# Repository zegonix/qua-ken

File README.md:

**This repository has been moved to [another git server](https://git.krampf.ch/zegonix/qua-ken).**

# qua-ken
this repository holds the design resources for the open source keyboard 'qua-ken'. The qua-ken is heavily inspired by [Josef Adamčík](https://github.com/josefadamcik)'s [Sofle](https://github.com/josefadamcik/SofleKeyboard) and copies its layout. The qua-ken is basically a Sofle modified to meet my custom keyboard standards. The PCB is split into main board and daughter board which holds the connectors. The qua-ken uses more a powerful ARM controller with much more program memory allowing the use of more software features. For the connection of the two halves a 4P4C connector is used as the TRRS connector shorts some of the lines when plugging/unplugging the cable. Currently planned are PCB silicone dumbbell gasket mount and plate top mount. The case is planned as screwless design opening from the top for ease of access. I also think about using the ball catch system gaining popularity, but since I have no experience with mechanical design, I am unsure whether I can manage that in a reasonable amount of revisions.

# Status
~~I just started and am currently working on the PCB. Once the PCB is tested, I will start with the case.~~
I just got the PCBs, it works perfectly fine appart from the encoders, which only work if the left half is master (connected to the computer). I am now starting with the case design and will fix the encoders at some point (just software).

# Licensing
Software (QMK) is licensed under GPL 2.0, With PCB and case designs you are free to do as you will.

# Can you buy this keyboard when it's finished?
Yes and No. I will not open shop and sell the keyboard, but the resources are free and open, so you can order all the parts yourself.

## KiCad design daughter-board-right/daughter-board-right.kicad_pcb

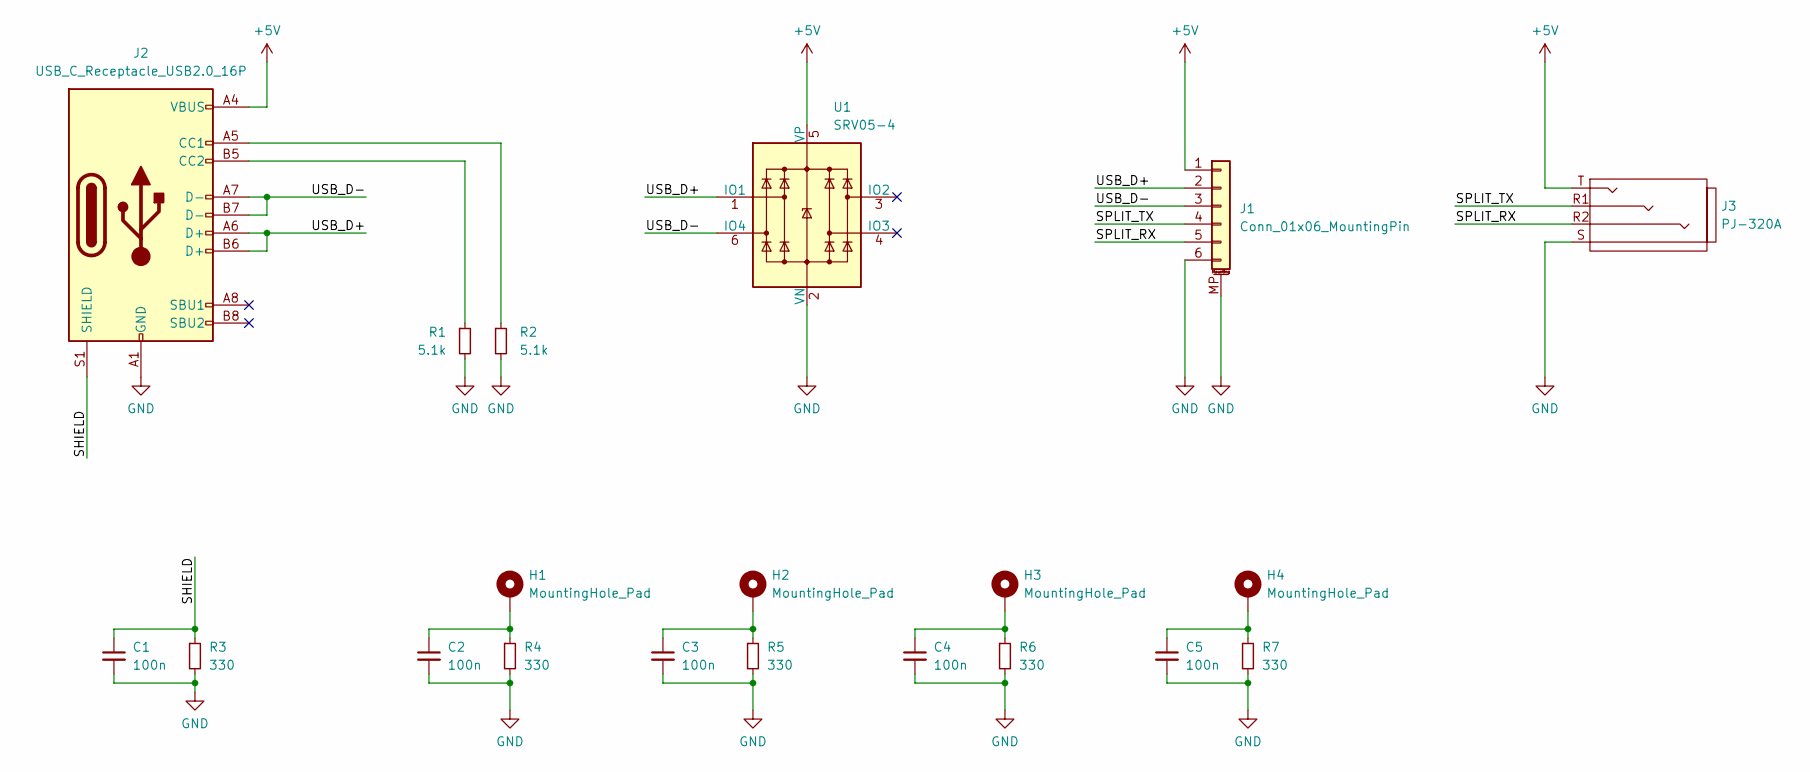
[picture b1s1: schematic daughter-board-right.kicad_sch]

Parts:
C1, C2, C3, C4, C5: 100n; C_0603_1608Metric
H1, H2, H3, H4: MountingHole_Pad; MountingHole_2.2mm_M2_DIN965_Pad_TopBottom
J1: Conn_01x06_MountingPin; JST_SH_SM06B-SRSS-TB_1x06-1MP_P1.00mm_Horizontal
J2: USB_C_Receptacle_USB2.0_16P; USB_C_Receptacle_HRO_TYPE-C-31-M-12
J3: PJ-320A; TRRS_Receptable
R1, R2: 5.1k; R_0603_1608Metric
R3, R4, R5, R6, R7: 330; R_0603_1608Metric
U1: SRV05-4; SOT-23-6-routable

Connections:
+5V: J1.1, J2.A4 (VBUS), J2.A9 (VBUS), J2.B4 (VBUS), J2.B9 (VBUS), J3.T, U1.5 (VP)
/SHIELD: C1.1, J2.S1 (SHIELD), R3.1
/SPLIT_RX: J1.5, J3.R2
/SPLIT_TX: J1.4, J3.R1
/USB_D+: J1.2, J2.A6 (D+), J2.B6 (D+), U1.1 (IO1)
/USB_D-: J1.3, J2.A7 (D-), J2.B7 (D-), U1.6 (IO4)
GND: C1.2, C2.2, C3.2, C4.2, C5.2, J1.6, J1.MP (MountPin), J2.A1 (GND), J2.A12 (GND), J2.B1 (GND), J2.B12 (GND), J3.S, R1.2, R2.2, R3.2, R4.2, R5.2, R6.2, R7.2, U1.2 (VN)
unnamed: C2.1, H1.1, R4.1
unnamed: C3.1, H2.1, R5.1
unnamed: C4.1, H3.1, R6.1
unnamed: C5.1, H4.1, R7.1
unnamed: J2.A5 (CC1), R2.1
unnamed: J2.B5 (CC2), R1.1

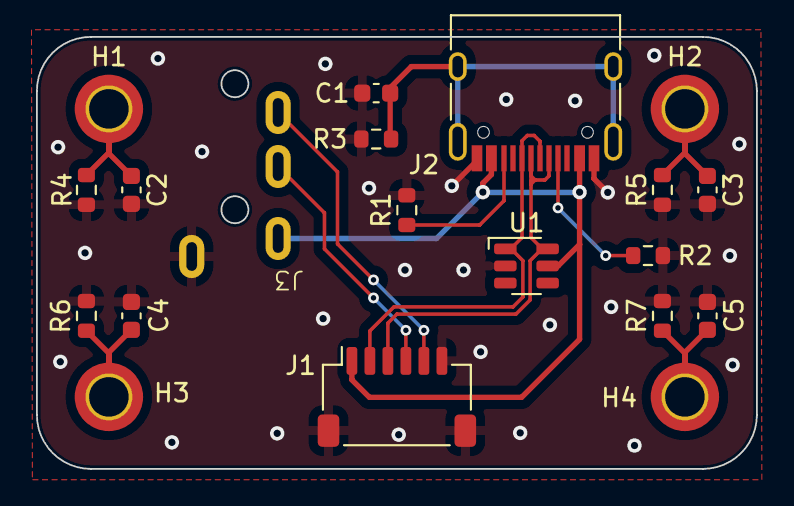
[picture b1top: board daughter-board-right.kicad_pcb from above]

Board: 2 copper layers, 40.0 x 24.0 mm, 20 parts (0 on the bottom side), 13 nets.

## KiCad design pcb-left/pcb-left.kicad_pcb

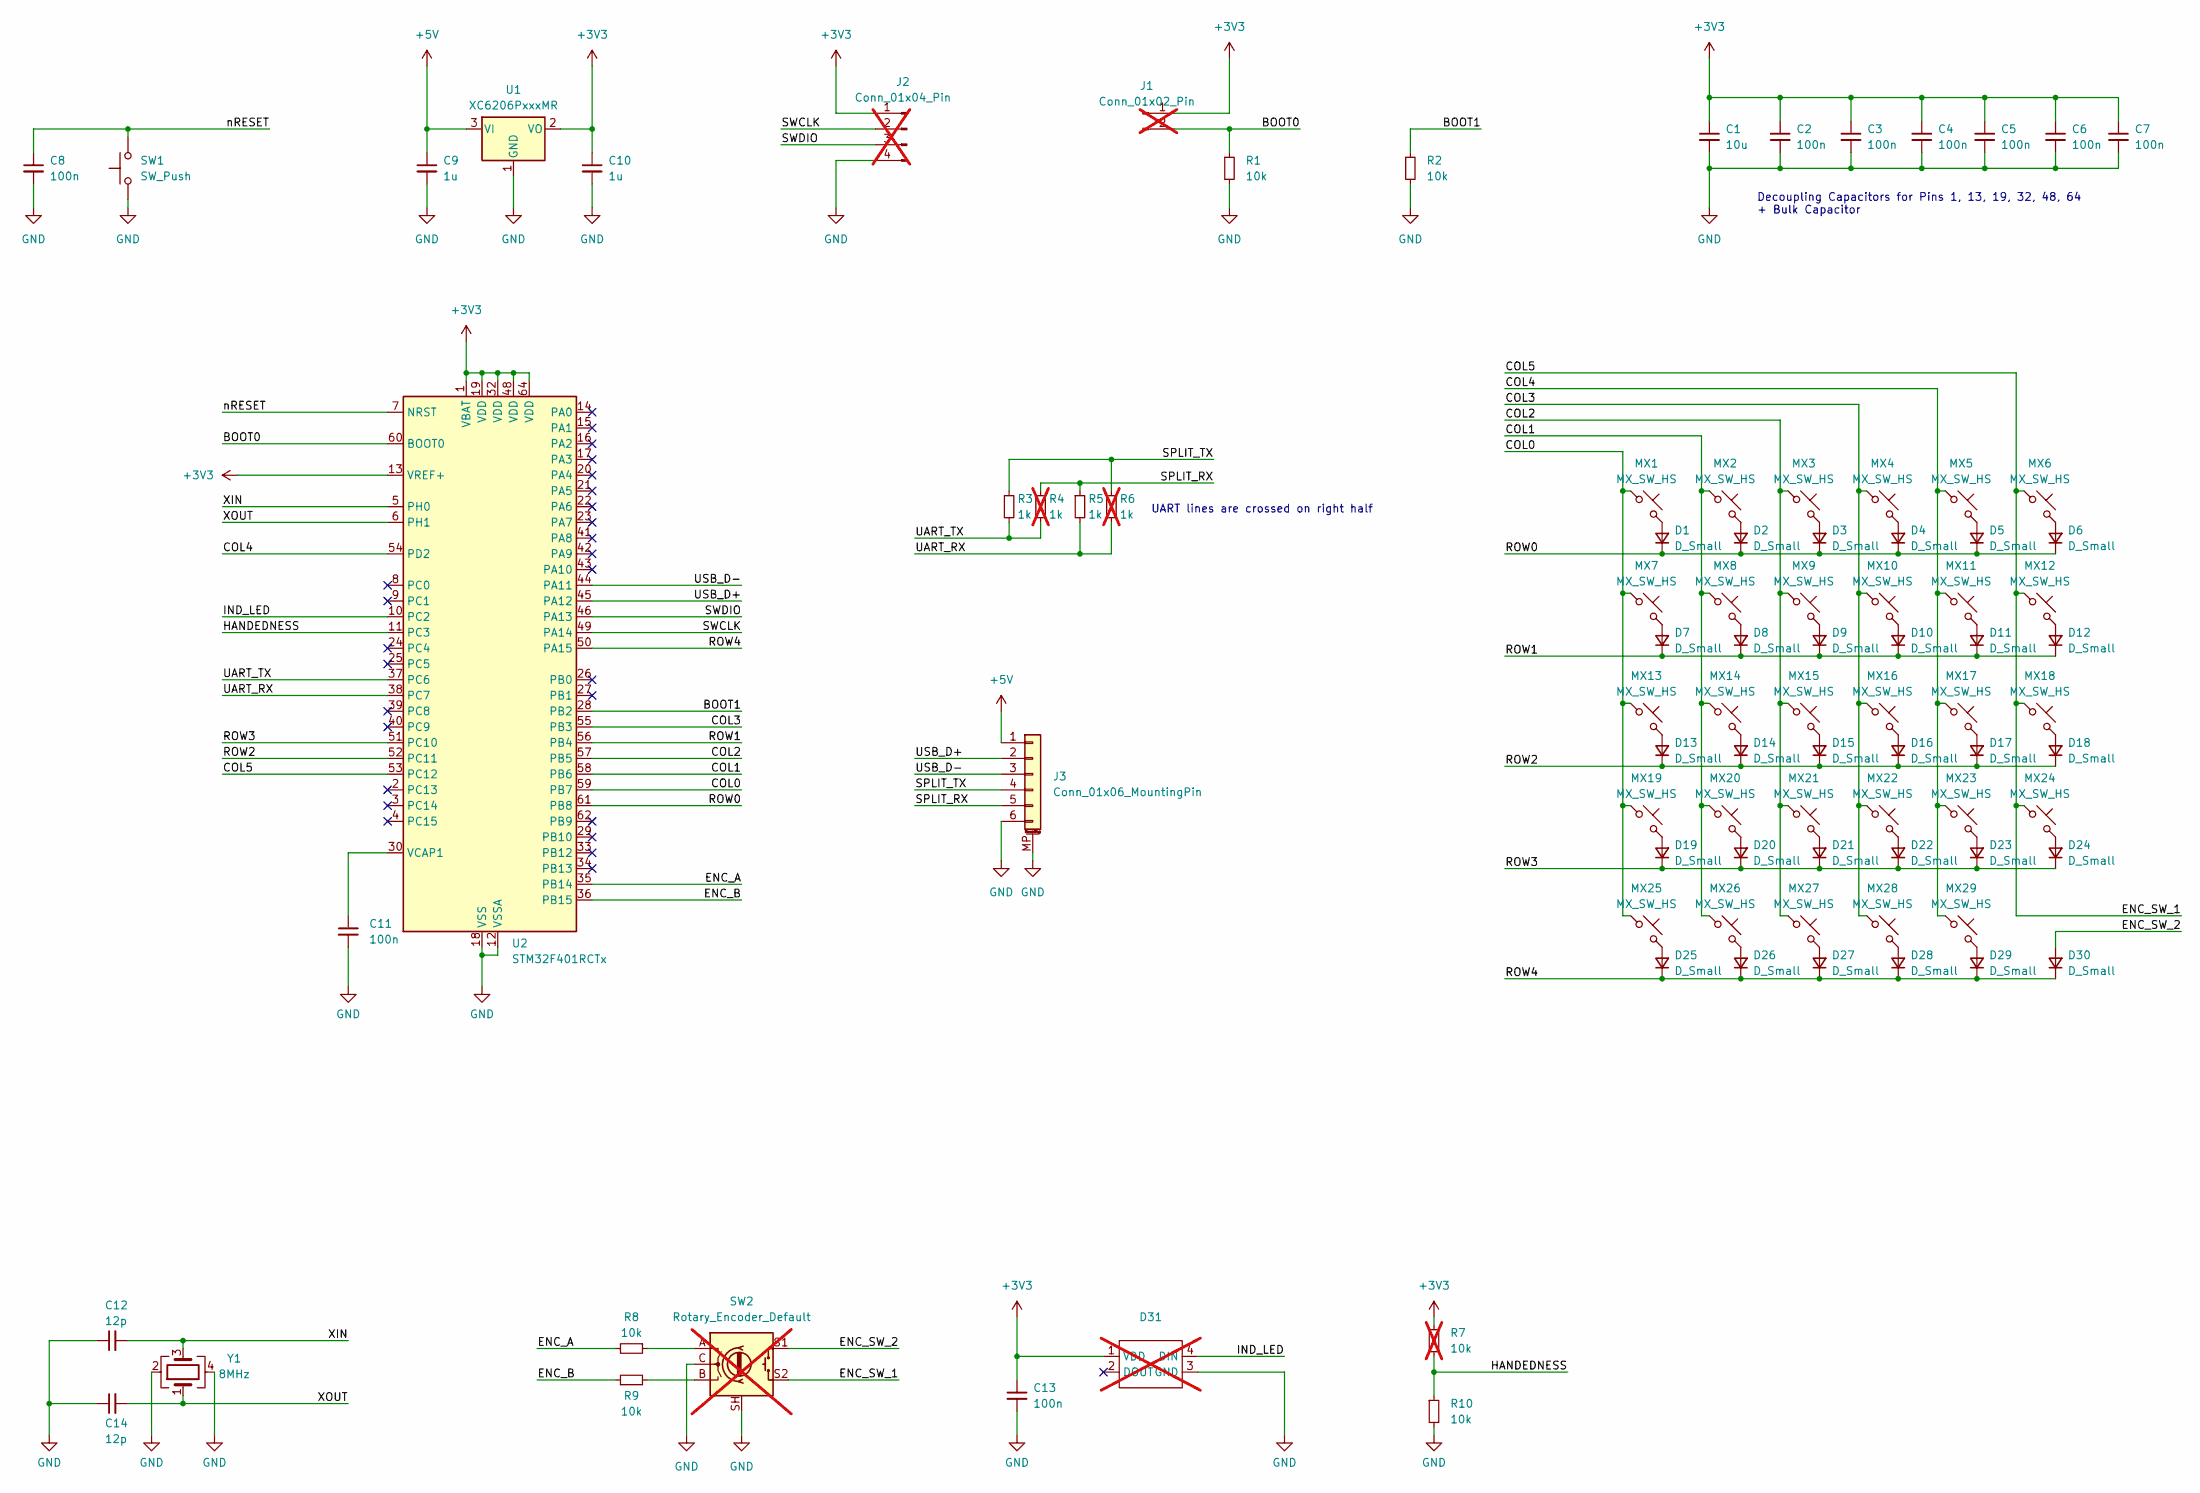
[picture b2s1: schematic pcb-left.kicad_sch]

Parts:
C1: 10u; C_0603_1608Metric
C2, C3, C4, C5, C6, C7, C8, C11, C13: 100n; C_0603_1608Metric
C9, C10: 1u; C_0603_1608Metric
C12, C14: 12p; C_0603_1608Metric
D1, D2, D3, D4, D5, D6, D7, D8, D9, D10, D11, D12, D13, D14, D15, D16, D17, D18, D19, D20, D21, D22, D23, D24, D25, D26, D27, D28, D29, D30: D_Small; D_SOD-123
D31: SK6812MINI-E_3.2x2.8_reverse_mount; not fitted
J1: Conn_01x02_Pin; PinHeader_1x02_P2.54mm_Vertical; not fitted
J2: Conn_01x04_Pin; PinHeader_1x04_P2.54mm_Vertical; not fitted
J3: Conn_01x06_MountingPin; JST_SH_SM06B-SRSS-TB_1x06-1MP_P1.00mm_Horizontal
MX1, MX2, MX3, MX4, MX5, MX6, MX7, MX8, MX9, MX10, MX11, MX12, MX13, MX14, MX15, MX16, MX17, MX18, MX19, MX20, MX21, MX22, MX23, MX24, MX25, MX26, MX27, MX28, MX29: MX_SW_HS; SW_MX_HS_1u
R1, R2, R8, R9, R10: 10k; R_0603_1608Metric
R3, R5: 1k; R_0603_1608Metric
R4, R6: 1k; R_0402_1005Metric; not fitted
R7: 10k; R_0603_1608Metric; not fitted
SW1: SW_Push; SW_SPST_TL3342
SW2: Rotary_Encoder_Default; RotaryEncoder_Bourns_Vertical_PEC12R-3x17F-Sxxxx; not fitted
U1: XC6206PxxxMR; SOT-23-3
U2: STM32F401RCTx; LQFP-64_10x10mm_P0.5mm
Y1: 8MHz; Crystal_SMD_3225-4Pin_3.2x2.5mm

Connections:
+3V3: C1.1, C2.1, C3.1, C4.1, C5.1, C6.1, C7.1, C10.1, C13.1, D31.1 (VDD), J1.1, J2.1, R7.1, U1.2 (VO), U2.1 (VBAT), U2.13 (VREF+), U2.19 (VDD), U2.32 (VDD), U2.48 (VDD), U2.64 (VDD)
+5V: C9.1, J3.1, U1.3 (VI)
/BOOT0: J1.2, R1.1, U2.60 (BOOT0)
/BOOT1: R2.1, U2.28 (PB2)
/COL0: MX1.1, MX7.1, MX13.1, MX19.1, MX25.1, U2.59 (PB7)
/COL1: MX2.1, MX8.1, MX14.1, MX20.1, MX26.1, U2.58 (PB6)
/COL2: MX3.1, MX9.1, MX15.1, MX21.1, MX27.1, U2.57 (PB5)
/COL3: MX4.1, MX10.1, MX16.1, MX22.1, MX28.1, U2.55 (PB3)
/COL4: MX5.1, MX11.1, MX17.1, MX23.1, MX29.1, U2.54 (PD2)
/COL5: MX6.1, MX12.1, MX18.1, MX24.1, SW2.S2, U2.53 (PC12)
/ENC_A: R8.2, U2.35 (PB14)
/ENC_B: R9.1, U2.36 (PB15)
/ENC_SW_2: D30.2 (A), SW2.S1
/HANDEDNESS: R7.2, R10.1, U2.11 (PC3)
/IND_LED: D31.4 (DIN), U2.10 (PC2)
/ROW0: D1.1 (K), D2.1 (K), D3.1 (K), D4.1 (K), D5.1 (K), D6.1 (K), U2.61 (PB8)
/ROW1: D7.1 (K), D8.1 (K), D9.1 (K), D10.1 (K), D11.1 (K), D12.1 (K), U2.56 (PB4)
/ROW2: D13.1 (K), D14.1 (K), D15.1 (K), D16.1 (K), D17.1 (K), D18.1 (K), U2.52 (PC11)
/ROW3: D19.1 (K), D20.1 (K), D21.1 (K), D22.1 (K), D23.1 (K), D24.1 (K), U2.51 (PC10)
/ROW4: D25.1 (K), D26.1 (K), D27.1 (K), D28.1 (K), D29.1 (K), D30.1 (K), U2.50 (PA15)
/SPLIT_RX: J3.5, R4.1, R5.1
/SPLIT_TX: J3.4, R3.1, R6.1
/SWCLK: J2.2, U2.49 (PA14)
/SWDIO: J2.3, U2.46 (PA13)
/UART_RX: R5.2, R6.2, U2.38 (PC7)
/UART_TX: R3.2, R4.2, U2.37 (PC6)
/USB_D+: J3.2, U2.45 (PA12)
/USB_D-: J3.3, U2.44 (PA11)
/XIN: C12.2, U2.5 (PH0), Y1.3
/XOUT: C14.2, U2.6 (PH1), Y1.1
/nRESET: C8.1, SW1.2, U2.7 (NRST)
GND: C1.2, C2.2, C3.2, C4.2, C5.2, C6.2, C7.2, C8.2, C9.2, C10.2, C11.2, C12.1, C13.2, C14.1, D31.3 (GND), J2.4, J3.6, J3.MP (MountPin), R1.2, R2.2, R10.2, SW1.1, SW2.C, SW2.SH, U1.1 (GND), U2.12 (VSSA), U2.18 (VSS), U2.31 (VSS), U2.47 (VSS), U2.63 (VSS), Y1.2, Y1.4
unnamed: D1.2 (A), MX1.2
unnamed: D2.2 (A), MX2.2
unnamed: D3.2 (A), MX3.2
unnamed: D4.2 (A), MX4.2
unnamed: D5.2 (A), MX5.2
unnamed: D6.2 (A), MX6.2
unnamed: D7.2 (A), MX7.2
unnamed: D8.2 (A), MX8.2
unnamed: D9.2 (A), MX9.2
unnamed: D10.2 (A), MX10.2
unnamed: D11.2 (A), MX11.2
unnamed: D12.2 (A), MX12.2
unnamed: D13.2 (A), MX13.2
unnamed: D14.2 (A), MX14.2
unnamed: D15.2 (A), MX15.2
unnamed: D16.2 (A), MX16.2
unnamed: D17.2 (A), MX17.2
unnamed: D18.2 (A), MX18.2
unnamed: D19.2 (A), MX19.2
unnamed: D20.2 (A), MX20.2
unnamed: D21.2 (A), MX21.2
unnamed: D22.2 (A), MX22.2
unnamed: D23.2 (A), MX23.2
unnamed: D24.2 (A), MX24.2
unnamed: D25.2 (A), MX25.2
unnamed: D26.2 (A), MX26.2
unnamed: D27.2 (A), MX27.2
unnamed: D28.2 (A), MX28.2
unnamed: D29.2 (A), MX29.2
unnamed: R8.1, SW2.A
unnamed: R9.2, SW2.B
unnamed: C11.1, U2.30 (VCAP1)

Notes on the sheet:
Decoupling Capacitors for Pins 1, 13, 19, 32, 48, 64 + Bulk Capacitor
UART lines are crossed on right half

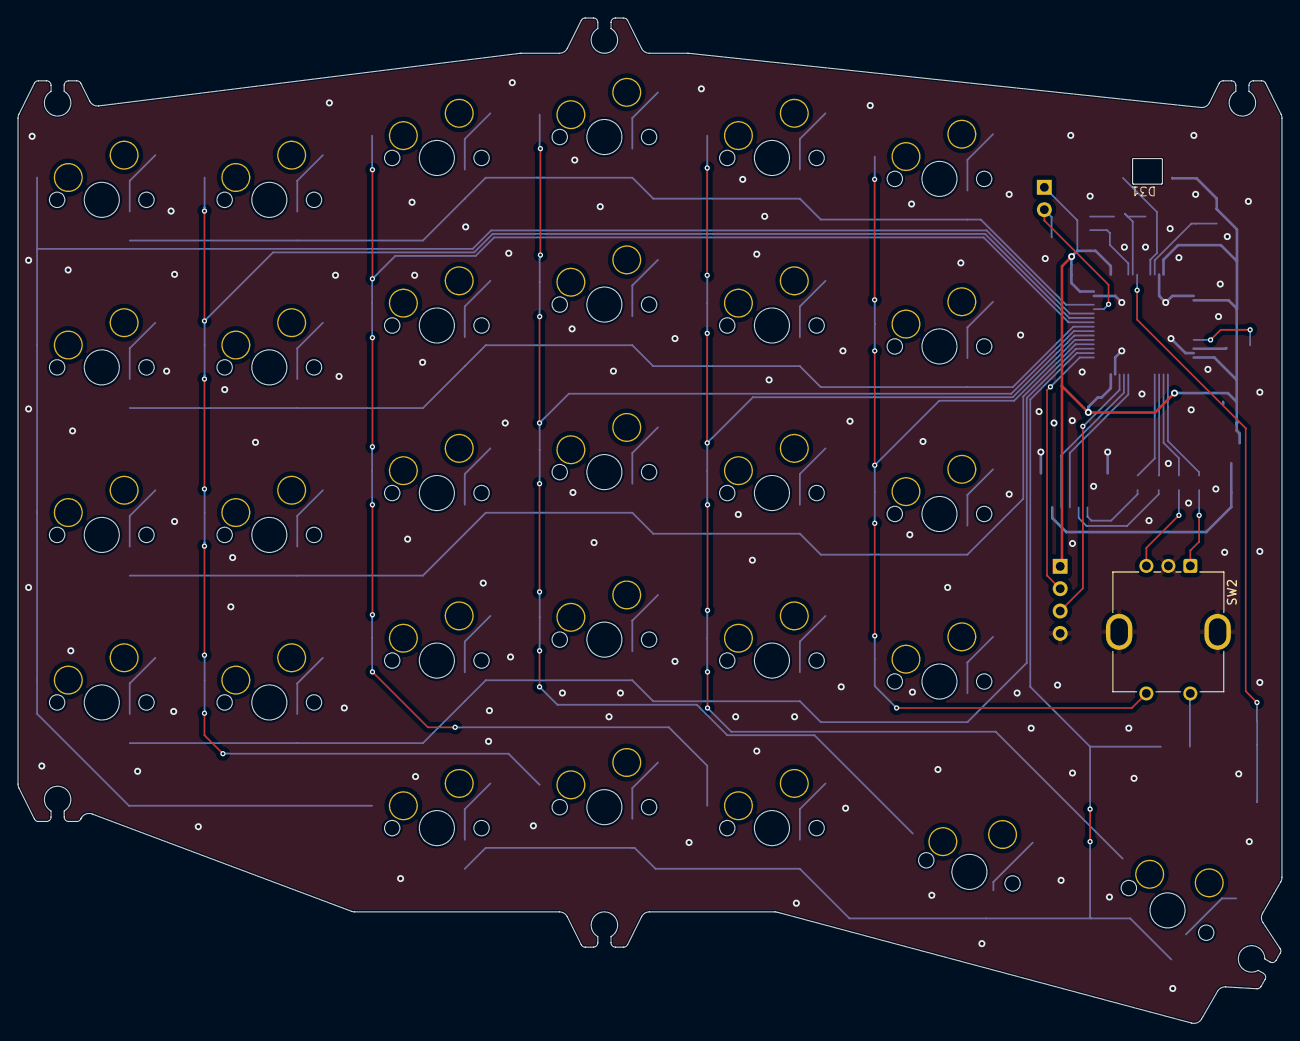
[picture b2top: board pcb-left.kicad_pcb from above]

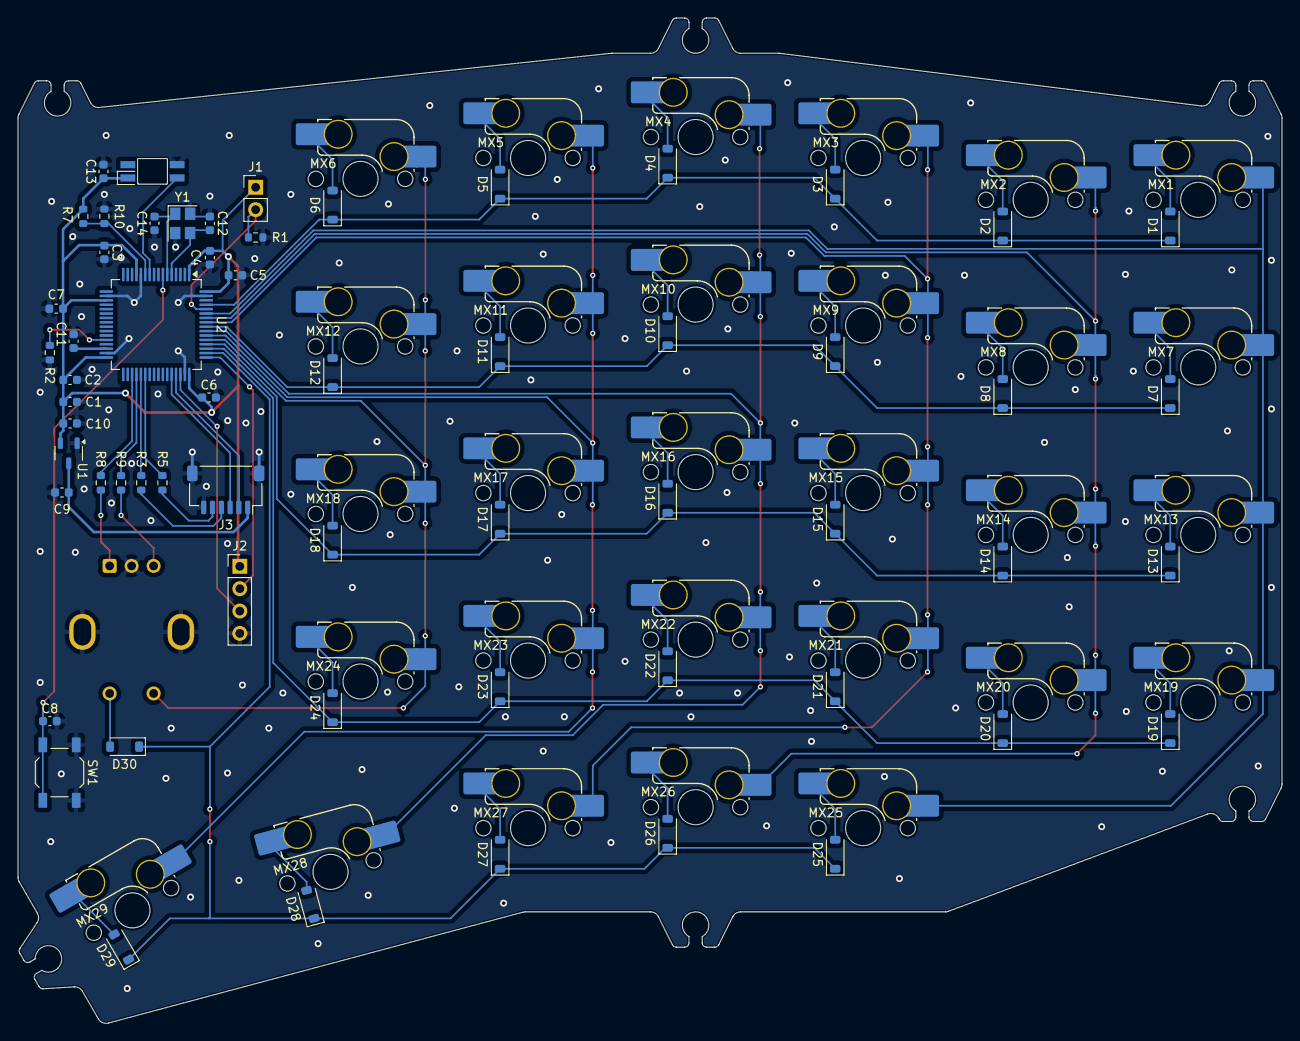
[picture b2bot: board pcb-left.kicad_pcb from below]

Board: 2 copper layers, 143.7 x 114.3 mm, 90 parts (88 on the bottom side), 64 nets.

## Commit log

2024-03-07 schematics review with scgh
2024-03-07 updated Readme file
2024-03-21 layout ready for review
2024-03-30 removed one switch from the thumb cluster
2024-04-08 implemented findings from layout review (of right half), changed name to pcb-right, created project for left half
2024-04-14 moved daughter board to separate projects for left and right halves fixed layouts of daughter boards..
2024-04-15 added new/renamed folders and files forgotten during last commits finished pcb-left
2024-06-19 quick save
2024-08-26 finalised first version of pcbs for prototype order added openscad file for the left halfs case
2024-08-27 again
2024-09-10 stuff
2026-02-22 removed openscad project, the case will be done separately
2026-04-05 intermediate save
2026-04-27 archived repository
